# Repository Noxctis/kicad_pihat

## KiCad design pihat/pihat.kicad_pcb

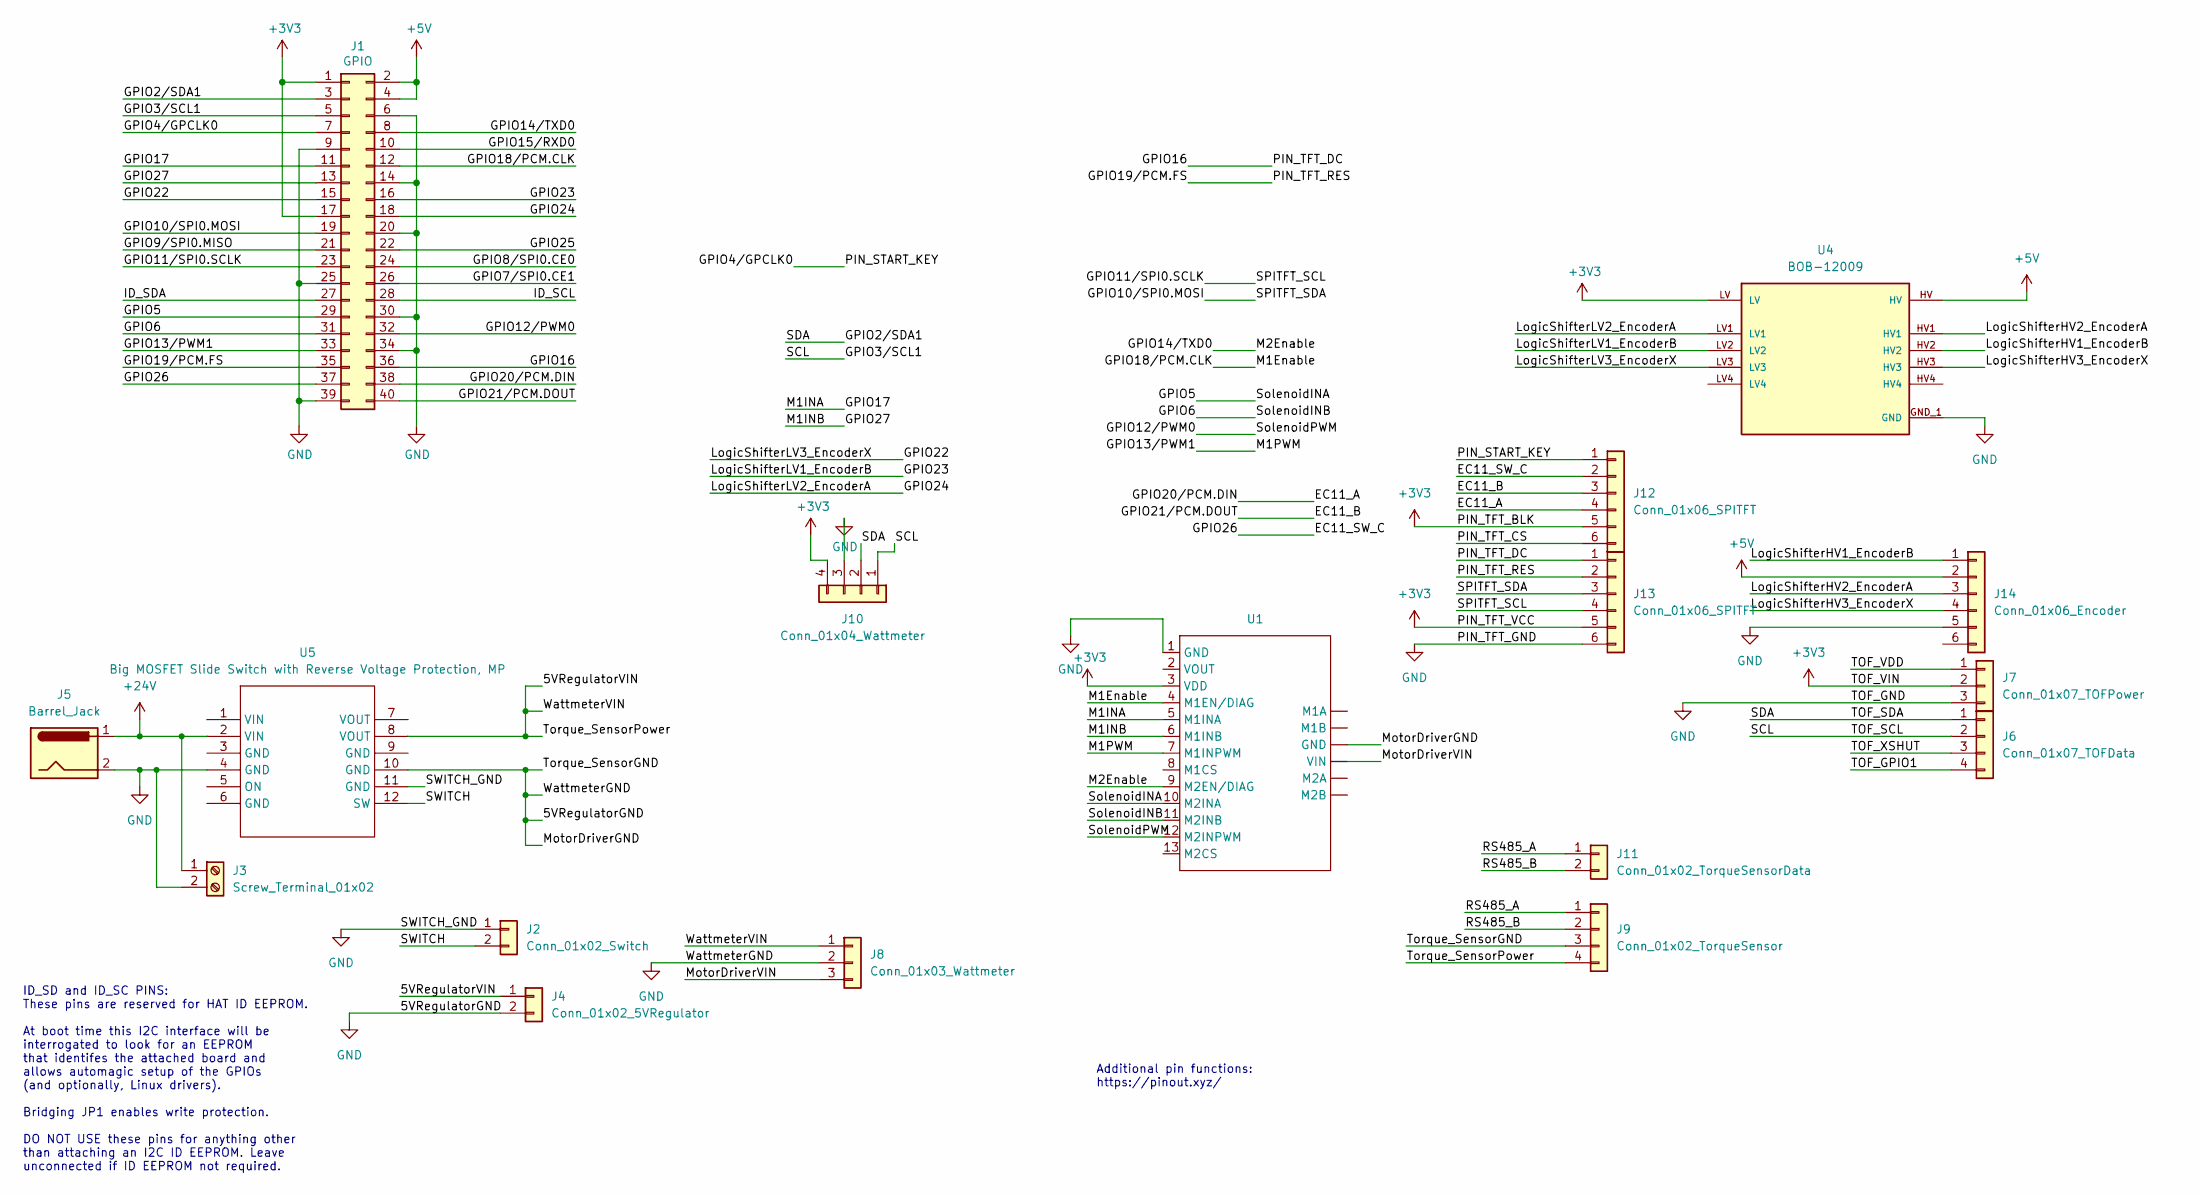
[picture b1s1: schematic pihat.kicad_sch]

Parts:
J1: GPIO; PinSocket_2x20_P2.54mm_Vertical
J2: Conn_01x02_Switch; TerminalBlock_Phoenix_MKDS-1,5-2-5.08_1x02_P5.08mm_Horizont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
J3: Screw_Terminal_01x02; TerminalBlock_Phoenix_MKDS-1,5-2-5.08_1x02_P5.08mm_Horizont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
J4: Conn_01x02_5VRegulator; TerminalBlock_Phoenix_MKDS-1,5-2-5.08_1x02_P5.08mm_Horizont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
J5: Barrel_Jack; BarrelJack_Horizontal
J6: Conn_01x07_TOFData; PinSocket_1x04_P2.54mm_Vertical
J7: Conn_01x07_TOFPower; PinSocket_1x03_P2.54mm_Vertical
J8: Conn_01x03_Wattmeter; TerminalBlock_Phoenix_MKDS-1,5-3-5.08_1x03_P5.08mm_Horizont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
J9: Conn_01x02_TorqueSensor; PinSocket_1x04_P2.54mm_Vertical
J10: Conn_01x04_Wattmeter; TerminalBlock_Phoenix_MKDS-1,5-4-5.08_1x04_P5.08mm_Horizont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
J11: Conn_01x02_TorqueSensorData; PinSocket_1x02_P2.54mm_Vertical
J12, J13: Conn_01x06_SPITFT; PinSocket_1x06_P2.54mm_Vertical
J14: Conn_01x06_Encoder; PinSocket_1x06_P2.54mm_Vertical
U1: DualVNH5019
U4: BOB-12009; CONV_BOB-12009; PARTREV 01
U5: Big MOSFET Slide Switch with Reverse Voltage Prot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; Big MOSFET Slide Switch with Reverse Voltage Protection, MP

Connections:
+3V3: J1.1, J1.17, J7.2, J10.4, J12.5, J13.5, U1.3 (VDD), U4.LV
+5V: J1.2, J1.4, J14.2, U4.HV
+24V: J3.1, J5.1, U5.2 (VIN)
/5VRegulatorVIN: J4.1, J8.1, J9.4, U5.8 (VOUT)
/EC11_A: J1.38, J12.4
/EC11_B: J1.40, J12.3
/EC11_SW_C: J1.37, J12.2
/GPIO2/SDA1: J1.3, J6.1, J10.2
/GPIO3/SCL1: J1.5, J6.2, J10.1
/GPIO4/GPCLK0: J1.7, J12.1
/GPIO5: J1.29, U1.10 (M2INA)
/GPIO6: J1.31, U1.11 (M2INB)
/GPIO7/SPI0.CE1: J1.26
/GPIO8/SPI0.CE0: J1.24
/GPIO9/SPI0.MISO: J1.21
/GPIO10/SPI0.MOSI: J1.19, J13.3
/GPIO11/SPI0.SCLK: J1.23, J13.4
/GPIO12/PWM0: J1.32, U1.12 (M2INPWM)
/GPIO13/PWM1: J1.33, U1.7 (M1INPWM)
/GPIO14/TXD0: J1.8, U1.9 (M2EN/DIAG)
/GPIO15/RXD0: J1.10
/GPIO16: J1.36, J13.1
/GPIO17: J1.11, U1.5 (M1INA)
/GPIO18/PCM.CLK: J1.12, U1.4 (M1EN/DIAG)
/GPIO19/PCM.FS: J1.35, J13.2
/GPIO22: J1.15, U4.LV3
/GPIO23: J1.16, U4.LV2
/GPIO24: J1.18, U4.LV1
/GPIO25: J1.22
/GPIO27: J1.13, U1.6 (M1INB)
/ID_SCL: J1.28
/ID_SDA: J1.27
/LogicShifterHV1_EncoderB: J14.1, U4.HV2
/LogicShifterHV2_EncoderA: J14.3, U4.HV1
/LogicShifterHV3_EncoderX: J14.4, U4.HV3
/MotorDriverVIN: J8.3, U1. (M1A)
/PIN_TFT_CS: J12.6
/RS485_A: J9.1, J11.1
/RS485_B: J9.2, J11.2
/SWITCH: J2.2, U5.12 (SW)
/TOF_GPIO1: J6.4
/TOF_VDD: J7.1
/TOF_XSHUT: J6.3
GND: J1.6, J1.9, J1.14, J1.20, J1.25, J1.30, J1.34, J1.39, J2.1, J3.2, J4.2, J5.2, J7.3, J8.2, J9.3, J10.3, J13.6, J14.5, U1. (M1A), U1.1 (GND), U4.GND_1 (GND), U4.GND_2 (GND), U5.4 (GND), U5.10 (GND), U5.11 (GND)

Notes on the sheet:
Additional pin functions: https://pinout.xyz/
ID_SD and ID_SC PINS: These pins are reserved for HAT ID EEPROM. At boot time this I2C interface will be interrogated to look for an EEPROM that identifes the attached board and allows automagic setup of the GPIOs (and optionally, Linux drivers). Bridging JP1 enables write protection. DO NOT USE th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

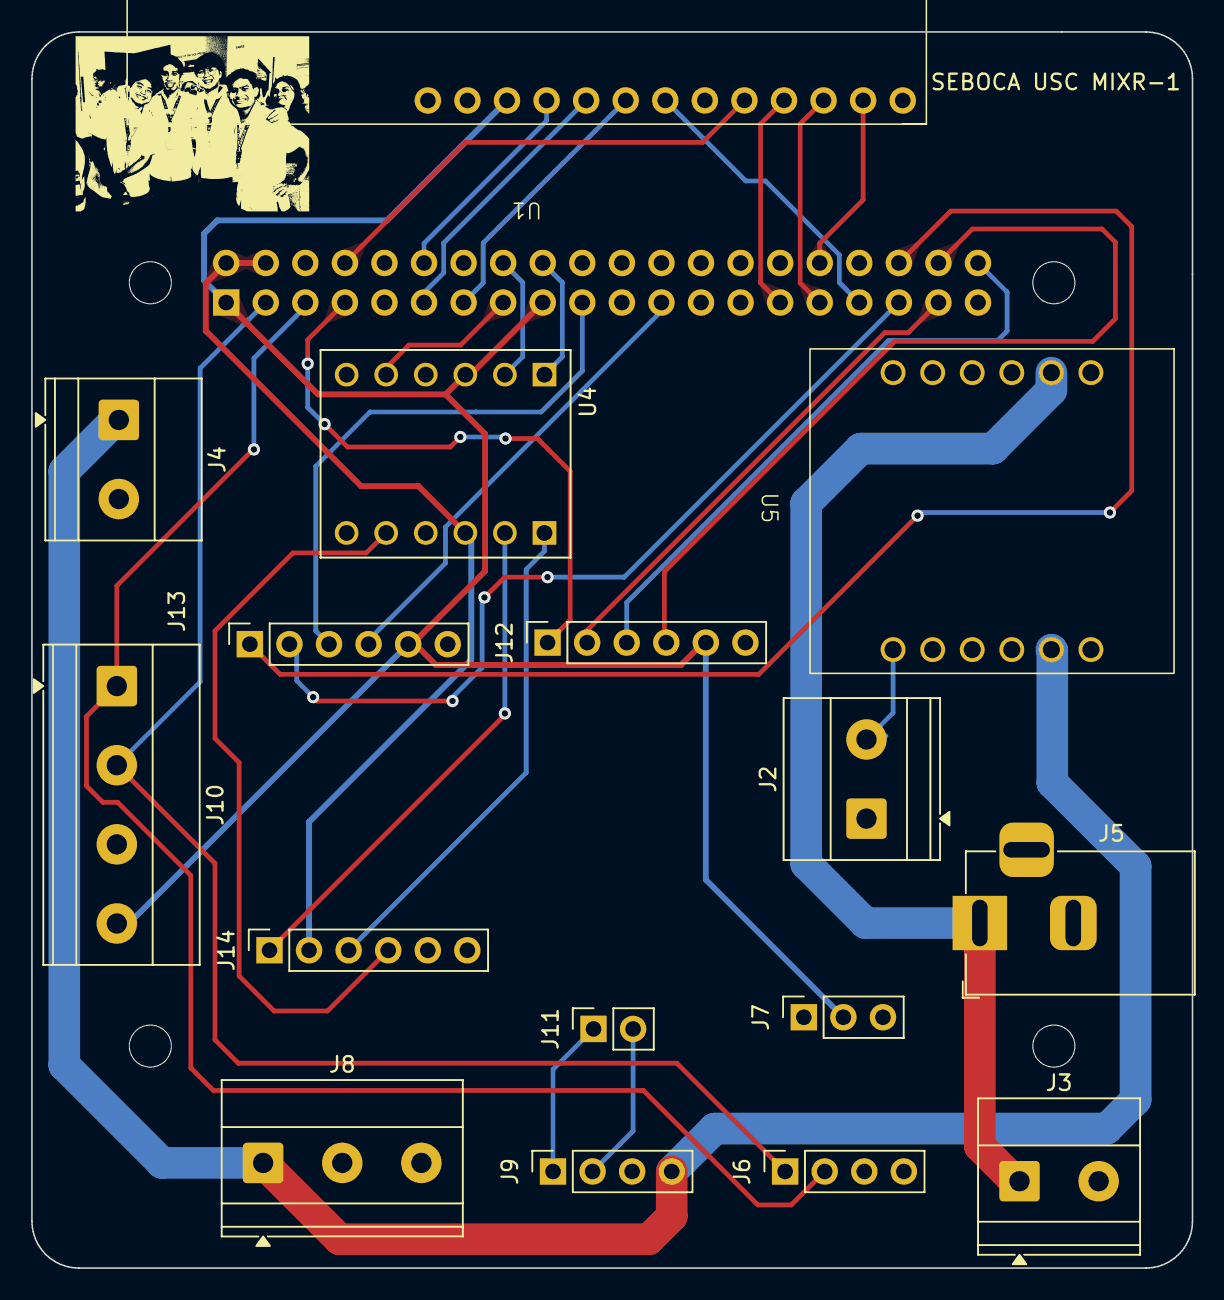
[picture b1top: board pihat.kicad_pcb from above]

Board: 2 copper layers, 74.5 x 79.3 mm, 21 parts (1 on the bottom side), 32 nets.

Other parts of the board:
MH1, MH2, MH3, MH4: MountingHole_2.7mm_M2.5

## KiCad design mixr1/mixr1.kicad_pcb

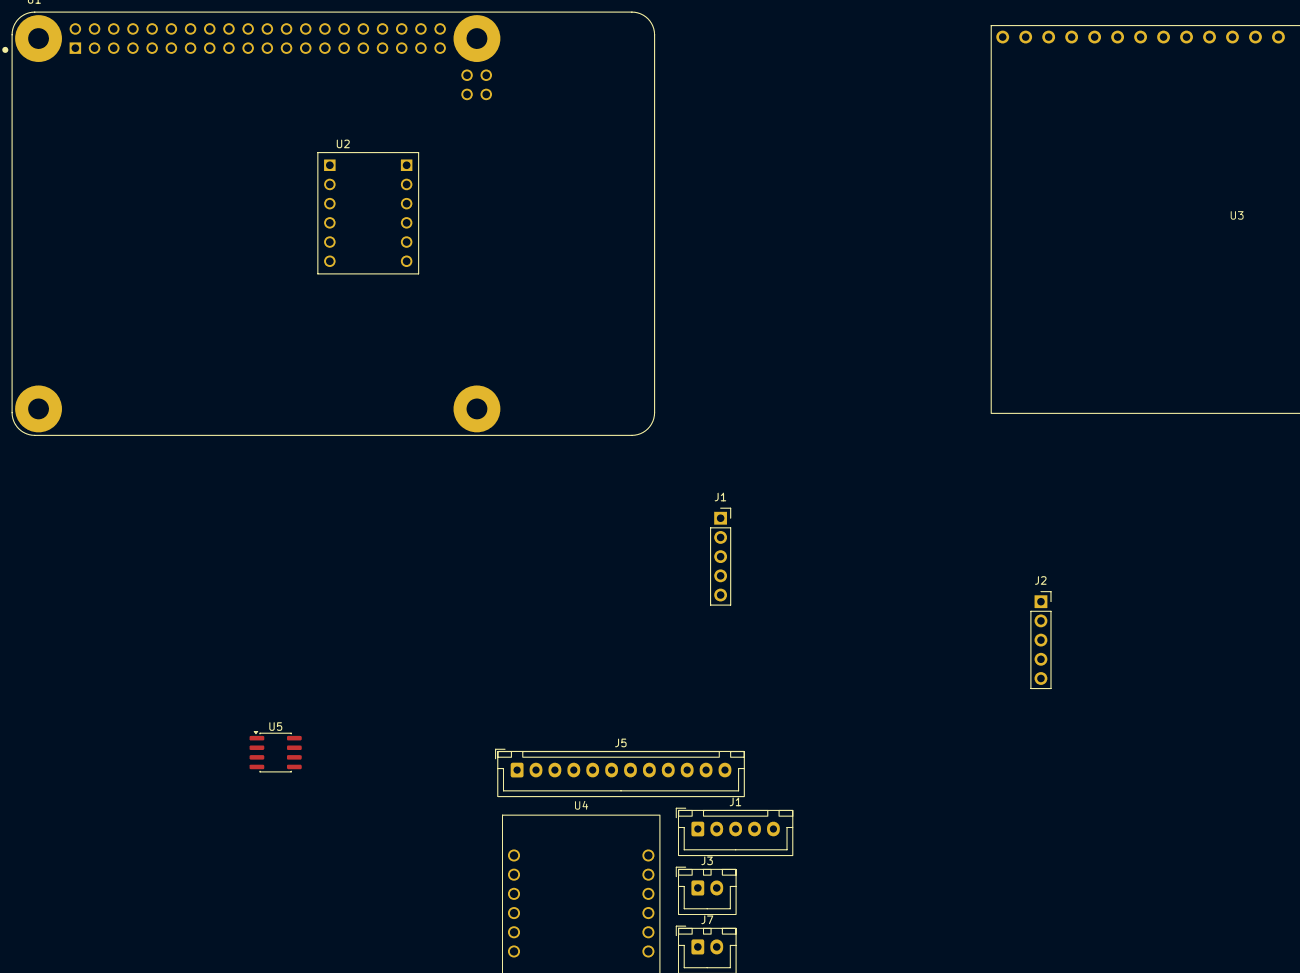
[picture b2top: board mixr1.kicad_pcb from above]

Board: 2 copper layers, 11 parts (0 on the bottom side), 31 nets, no tracks yet.

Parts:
J1: Conn_01x05_Socket_Encoder; PinSocket_1x05_P2.54mm_Vertical
J1#2: Conn_01x05_Encoder; JST_XH_B5B-XH-A_1x05_P2.50mm_Vertical
J2: Conn_01x05_Socket_Rotary; PinSocket_1x05_P2.54mm_Vertical
J3: Conn_01x02_TorqueSensorData; JST_XH_B2B-XH-A_1x02_P2.50mm_Vertical
J5: Conn_01x12_SPITFT; JST_XH_B12B-XH-A_1x12_P2.50mm_Vertical
J7: Conn_01x02_TorqueSensorPower; JST_XH_B2B-XH-A_1x02_P2.50mm_Vertical
U1: RASPBERRY_PI_4B_4GB; MODULE_RASPBERRY_PI_4B_4GB
U2: BOB-12009; CONV_BOB-12009
U3: DualVNH5019
U4: Big MOSFET Slide Switch with Reverse Voltage Prot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; Big MOSFET Slide Switch with Reverse Voltage Protection, MP
U5: INA219AxD; SOIC-8_3.9x4.9mm_P1.27mm

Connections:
+3.3V: J2.5, J5.5, J5.11, U1.1 (3V3), U1.17 (3V3), U2.LV, U3.3 (VDD)
+5V: J1.2, J1#2.2, U1.2 (5V), U1.4 (5V), U2.HV
/5VRegulatorGND: J7.1, U4.10 (GND), U5.6 (GND)
/5VRegulatorVIN: J7.2, U4.8 (VOUT), U5.8 (IN+)
/EC11_A: J2.3, J5.4, U1.38 (GPIO20)
/EC11_B: J2.2, J5.3, U1.40 (GPIO21)
/EC11_SW_C: J2.1, J5.2, U1.37 (GPIO26)
/LogicShifterHV1_EncoderB: J1#2.1, U2.HV2
/LogicShifterHV2_EncoderA: J1#2.3, U2.HV1
/LogicShifterHV3_EncoderX: J1#2.4, U2.HV3
/LogicShifterLV1_EncoderB: J1.1, U1.16 (GPIO23/GPIO_GEN4), U2.LV2
/LogicShifterLV2_EncoderA: J1.3, U1.18 (GPIO24/GPIO_GEN5), U2.LV1
/LogicShifterLV3_EncoderX: J1.4, U1.15 (GPIO22/GPIO_GEN3), U2.LV3
/M1Enable: U1.12 (GPIO18/GPIO_GEN1), U3.4 (M1EN/DIAG)
/M1INA: U1.11 (GPIO17/GPIO_GEN0), U3.5 (M1INA)
/M1INB: U1.13 (GPIO27/GPIO_GEN2), U3.6 (M1INB)
/M1PWM: U1.33 (GPIO13), U3.7 (M1INPWM)
/M2Enable: U1.8 (GPIO14/TXD0), U3.9 (M2EN/DIAG)
/PIN_START_KEY: J5.1, U1.7 (GPIO4/GPIO_GCKL)
/PIN_TFT_CS: J5.6, U1.22 (GPIO25/GPIO_GEN6)
/PIN_TFT_DC: J5.7, U1.36 (GPIO16)
/PIN_TFT_RES: J5.8, U1.35 (GPIO19)
/SCL: U1.5 (GPIO3/SCL1), U5.4 (SCL)
/SDA: U1.3 (GPIO2/SDA1), U5.3 (SDA)
/SPITFT_SCL: J5.10, U1.23 (GPIO11/SPI_SCLK)
/SPITFT_SDA: J5.9, U1.19 (GPIO10/SPI_MOSI)
/SolenoidINA: U1.29 (GPIO5), U3.10 (M2INA)
/SolenoidINB: U1.31 (GPIO6), U3.11 (M2INB)
/SolenoidPWM: U1.32 (GPIO12), U3.12 (M2INPWM)
GND: J1.5, J1#2.5, J2.4, J5.12, U1.6 (GND), U1.9 (GND), U1.14 (GND), U1.20 (GND), U1.25 (GND), U1.30 (GND), U1.34 (GND), U1.39 (GND), U2.GND_1 (GND), U2.GND_2 (GND), U3.1 (GND), U4.4 (GND)
SHIELD: U1.S1 (SHIELD), U1.S2 (SHIELD), U1.S3 (SHIELD), U1.S4 (SHIELD)
